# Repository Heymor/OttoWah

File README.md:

# OttoWah
A simple Auto-Wah pedal design taken from Denton J. Dailey's book, *Electronics For Guitarists*.

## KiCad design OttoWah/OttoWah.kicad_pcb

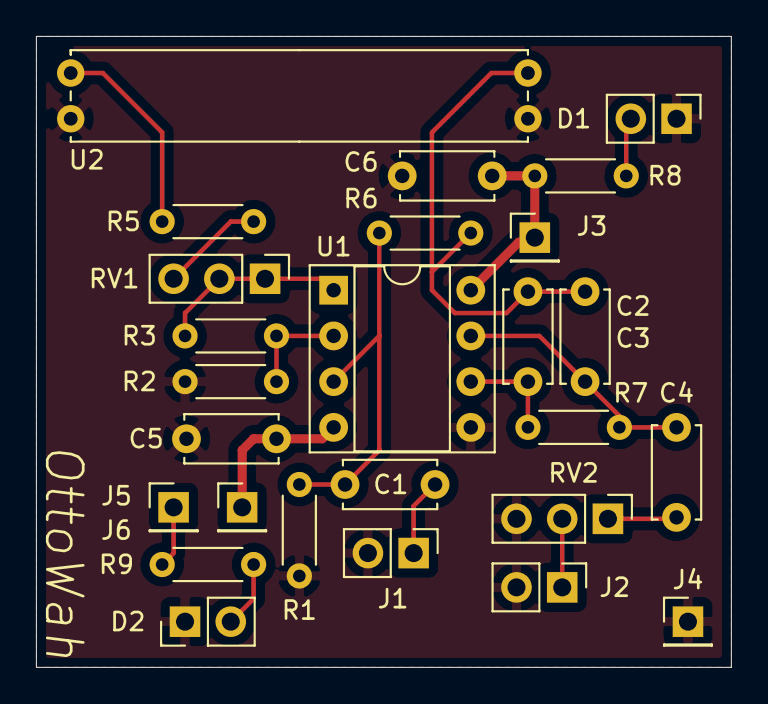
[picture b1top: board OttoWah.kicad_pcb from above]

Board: 2 copper layers, 38.6 x 35.1 mm, 26 parts (0 on the bottom side), 17 nets.

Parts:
C1: 0.1uF; C_Disc_D5.0mm_W2.5mm_P5.00mm
C2, C3: 0.01uF; C_Disc_D5.0mm_W2.5mm_P5.00mm
C4: 47uF; C_Disc_D5.0mm_W2.5mm_P5.00mm
C5, C6: 10uF; C_Disc_D5.0mm_W2.5mm_P5.00mm
D1, D2: LED; PinHeader_1x02_P2.54mm_Vertical
J1, J2: Conn_01x02_Female; PinHeader_1x02_P2.54mm_Vertical
J3, J4, J5, J6: Conn_01x01_Female; PinHeader_1x01_P2.54mm_Vertical
R1, R3: 100k; R_Axial_DIN0204_L3.6mm_D1.6mm_P5.08mm_Horizontal
R2: 2.2k; R_Axial_DIN0204_L3.6mm_D1.6mm_P5.08mm_Horizontal
R5, R8, R9: 1k; R_Axial_DIN0204_L3.6mm_D1.6mm_P5.08mm_Horizontal
R6: 120k; R_Axial_DIN0204_L3.6mm_D1.6mm_P5.08mm_Horizontal
R7: 270k; R_Axial_DIN0204_L3.6mm_D1.6mm_P5.08mm_Horizontal
RV1: 25k_LIN; PinHeader_1x03_P2.54mm_Vertical
RV2: 10k_LOG; PinHeader_1x03_P2.54mm_Vertical
U1: TL072; DIP-8_W7.62mm_Socket
U2: Optocoupler

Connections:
+9V: C6.2, J3.1, R8.2, U1.8
-9V: C5.1, J5.1, U1.4
GND: C5.2, C6.1, D1.1, D2.1, J1.2, J2.2, J4.1, R1.2, R2.2, RV2.3, U1.5, U2.2, U2.4
unnamed: C1.1, R1.1, R6.2, U1.3
unnamed: C1.2, J1.1
unnamed: C2.1, R7.2, U1.6
unnamed: C2.2, C3.2, R6.1, U2.3
unnamed: C3.1, C4.1, R7.1, U1.7
unnamed: C4.2, RV2.1
unnamed: D1.2, R8.1
unnamed: D2.2, R9.1
unnamed: J2.1, RV2.2
unnamed: J6.1, R9.2
unnamed: R2.1, R3.2, U1.2
unnamed: R3.1, RV1.1, RV1.2, U1.1
unnamed: R5.1, U2.1
unnamed: R5.2, RV1.3

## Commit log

2021-03-31 Updated schematic
    - Added decoupling caps to power rails
    - Added power and effect on indicators
    - Began assigning footprints
2021-04-01 Finished preliminary layout and routing.
2021-04-05 First revision of pedal board - all footprints finalized
2021-04-05 Completely revamped layout and routing, and updated diode footprints. Should be ready for ordering!
2021-04-05 Ordered version
2022-04-14 Updated KiCad project and added LTSpice AC sim
